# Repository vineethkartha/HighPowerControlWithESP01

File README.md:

# HighPowerControlWithESP01
This is a circuit to use the ESP-01 to control 15A plugs that are usually used to 
connect high power devices like, induction stoves, water heaters etc.

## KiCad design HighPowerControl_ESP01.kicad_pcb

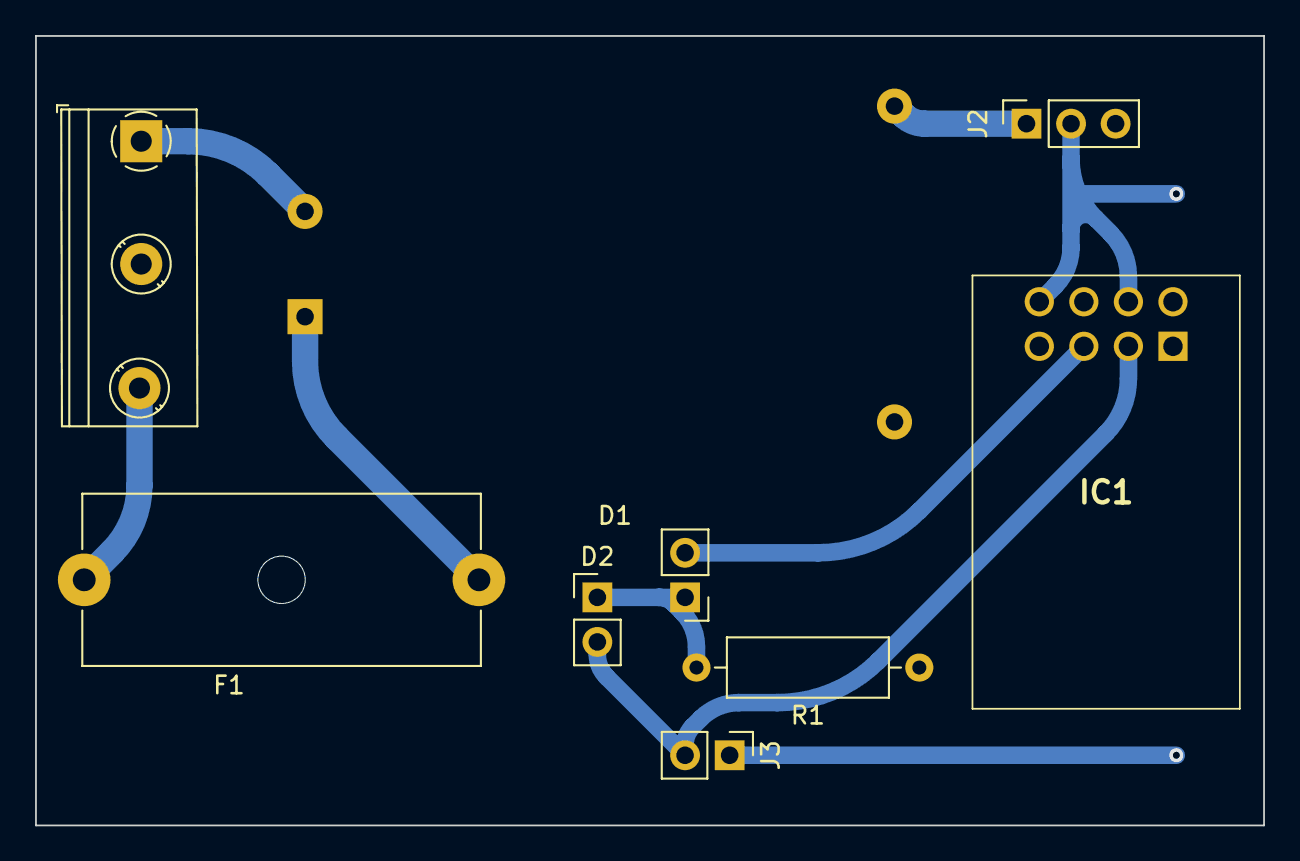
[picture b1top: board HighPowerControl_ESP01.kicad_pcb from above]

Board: 2 copper layers, 70.0 x 45.0 mm, 9 parts (1 on the bottom side), 9 nets.

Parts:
D1: WifiLED; PinHeader_1x02_P2.54mm_Vertical
D2: Relay LED; PinHeader_1x02_P2.54mm_Vertical
F1: Fuse; Fuseholder_Cylinder-5x20mm_Schurter_0031_8201_Horizontal_Op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
IC1: ESP-01; ESP01
J1: AC Input; TerminalBlock_Phoenix_MKDS-1,5-3-5.08_1x03_P6.6mm_Horizontal
J2: AMS1117Module; PinSocket_1x03_P2.54mm_Vertical
J3: To SSR; PinHeader_1x02_P2.54mm_Vertical
PS1: HLK-5M05; Converter_ACDC_HiLink_HLK-5Mxx
R1: 220; R_Axial_DIN0309_L9.0mm_D3.2mm_P12.70mm_Horizontal

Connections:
/3V3: IC1.6 (EN), IC1.8 (VCC), J2.2, J3.1
/5V: J2.1, PS1.4 (+Vout)
/AC_L: F1.1, J1.3
/AC_N: J1.1, PS1.2 (AC/N)
/GndL: IC1.1 (GND), J2.3, PS1.3 (-Vout), R1.1
/LED: D1.2 (A), IC1.3 (IO0)
/Relay: D2.2 (A), IC1.2 (IO2), J3.2
unnamed: D1.1 (K), D2.1 (K), R1.2
unnamed: F1.2, PS1.1 (AC/L)

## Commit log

2023-12-21 Basic circuit and PCB layout
2023-12-24 Flip the HiLInk AC-DC converter footprint
2023-12-26 Inverting logic of SSR
    when SSR is connected to the GPIO it causes an issue in the boot of ESP-01
    So the circuit was changed slightly based on the suggestions in https://arduino.stackexchange.com/questions/37303/esp8266-esp-01-not-booting-with-load-on-io-pin-2
